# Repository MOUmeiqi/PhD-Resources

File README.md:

# PhD-Resources
Source code repository for PhD on OCDM-aEITS

*** README ***

This repository (repo) contains the source code and some experimental results acquired during research of the thesis titled "Absolute Electrical Impedance Tomography and Spectroscopy - An Orthogonal Chirp Division Multiplexed (OCDM) Approach"
This thesis was authored by: Ezra Luke America and presented to the University of Cape Town for fulfilment of a Doctorate of Philosophy in Electrical Engineering.

The repo separated into four streams:
1) Source Codes
2) Misc. Experimental Results
3) Schematics
4) Misc. Images

*** Codes ***
The source codes components of the repo holds the source files that were used for the Arduino, MATLAB, uDAQ, and FPGA.
The code for the Arduino was used to control the system wide multiplexing.
The code for MATLAB was used to control the entire system and reconstruct images.
The code for the uDAQ_test_scripts were used to control a data acquisition card when initial tests were performed.
The code for the VHDL_CODE were used to control the ADC/DAC data acquisition board and FPGA.

*** Misc. Experimental Results ***
This folder contains 8 internal folders that hold a measurement frame for eight different positions of an anomaly.
To test this data, import the data to the MATLAB image_reconstruction code in the MATLAB folder.

*** Schematics ***
The schematics folder contains some system design schematics.

*** Misc. Images ***
This folder contains some reconstructed images using higher element FEM models.

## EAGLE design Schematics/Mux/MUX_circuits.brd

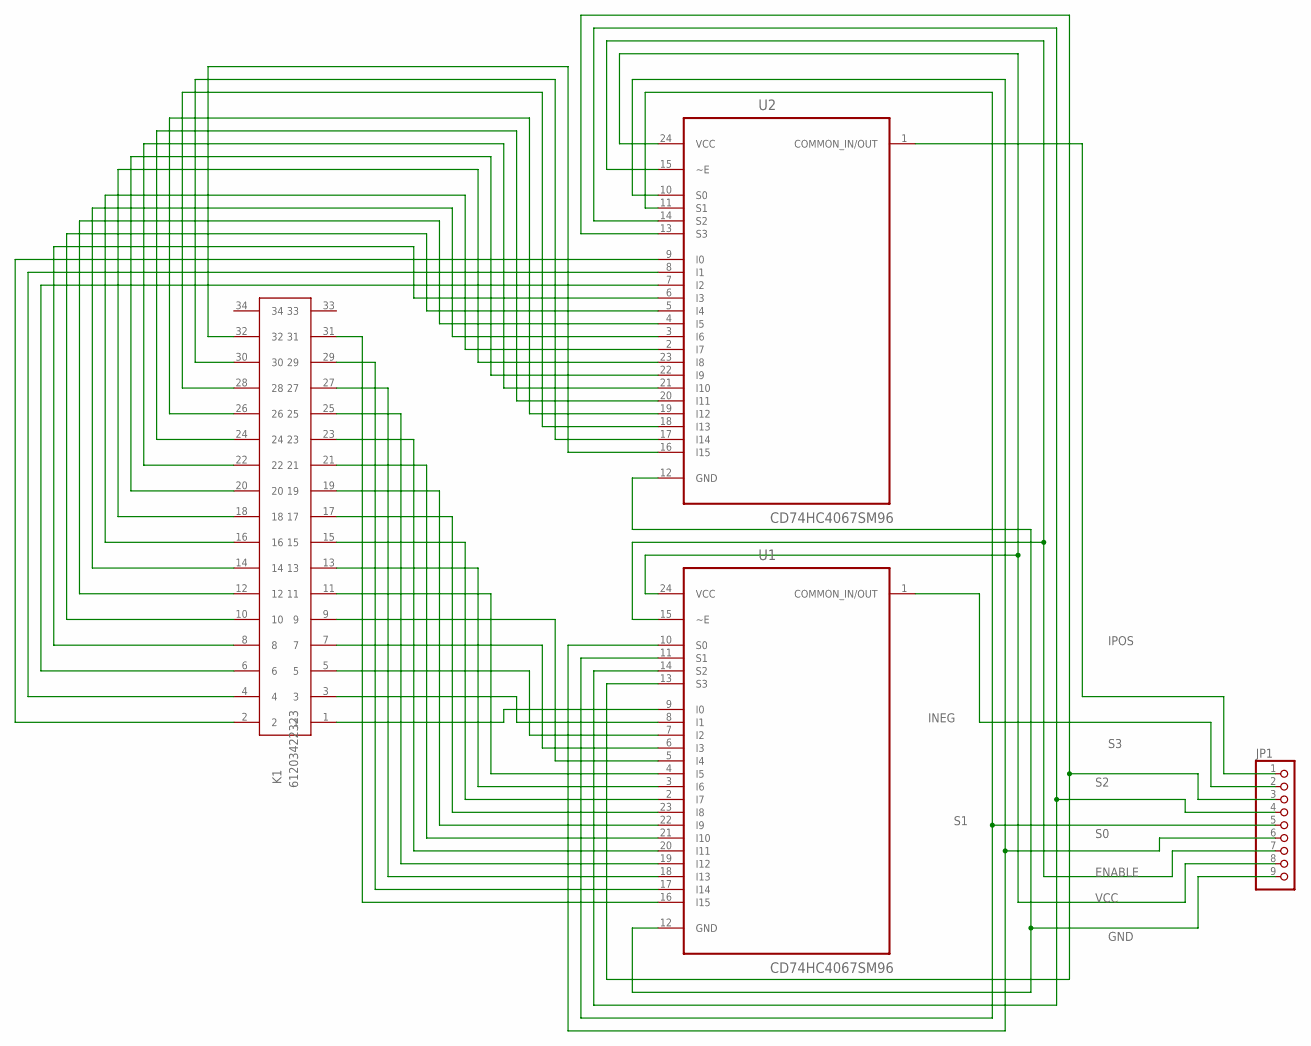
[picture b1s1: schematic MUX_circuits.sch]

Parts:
JP1: PINHD-1X9; 1X09
K1: 61203422323
U1, U2: CD74HC4067SM96; SOP65P780X200-24N

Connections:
ENABLE: JP1.7, U1.15 (~E), U2.15 (~E)
GND: JP1.9, U1.12 (GND), U2.12 (GND)
INEG: JP1.2, U1.1 (COMMON_IN/OUT)
IPOS: JP1.1, U2.1 (COMMON_IN/OUT)
unnamed: K1.1, U1.9 (I0)
unnamed: K1.2, U2.9 (I0)
unnamed: K1.3, U1.8 (I1)
unnamed: K1.5, U1.7 (I2)
unnamed: K1.7, U1.6 (I3)
unnamed: K1.9, U1.5 (I4)
unnamed: K1.11, U1.4 (I5)
unnamed: K1.13, U1.3 (I6)
unnamed: K1.15, U1.2 (I7)
unnamed: K1.17, U1.23 (I8)
unnamed: K1.19, U1.22 (I9)
unnamed: K1.21, U1.21 (I10)
unnamed: K1.23, U1.20 (I11)
unnamed: K1.25, U1.19 (I12)
unnamed: K1.27, U1.18 (I13)
unnamed: K1.29, U1.17 (I14)
unnamed: K1.31, U1.16 (I15)
unnamed: K1.4, U2.8 (I1)
unnamed: K1.6, U2.7 (I2)
unnamed: K1.8, U2.6 (I3)
unnamed: K1.10, U2.5 (I4)
unnamed: K1.12, U2.4 (I5)
unnamed: K1.14, U2.3 (I6)
unnamed: K1.16, U2.2 (I7)
unnamed: K1.18, U2.23 (I8)
unnamed: K1.20, U2.22 (I9)
unnamed: K1.22, U2.21 (I10)
unnamed: K1.24, U2.20 (I11)
unnamed: K1.26, U2.19 (I12)
unnamed: K1.28, U2.18 (I13)
unnamed: K1.30, U2.17 (I14)
unnamed: K1.32, U2.16 (I15)
S0: JP1.6, U1.10 (S0), U2.10 (S0)
S1: JP1.5, U1.11 (S1), U2.11 (S1)
S2: JP1.4, U1.14 (S2), U2.14 (S2)
S3: JP1.3, U1.13 (S3), U2.13 (S3)
VCC: JP1.8, U1.24 (VCC), U2.24 (VCC)

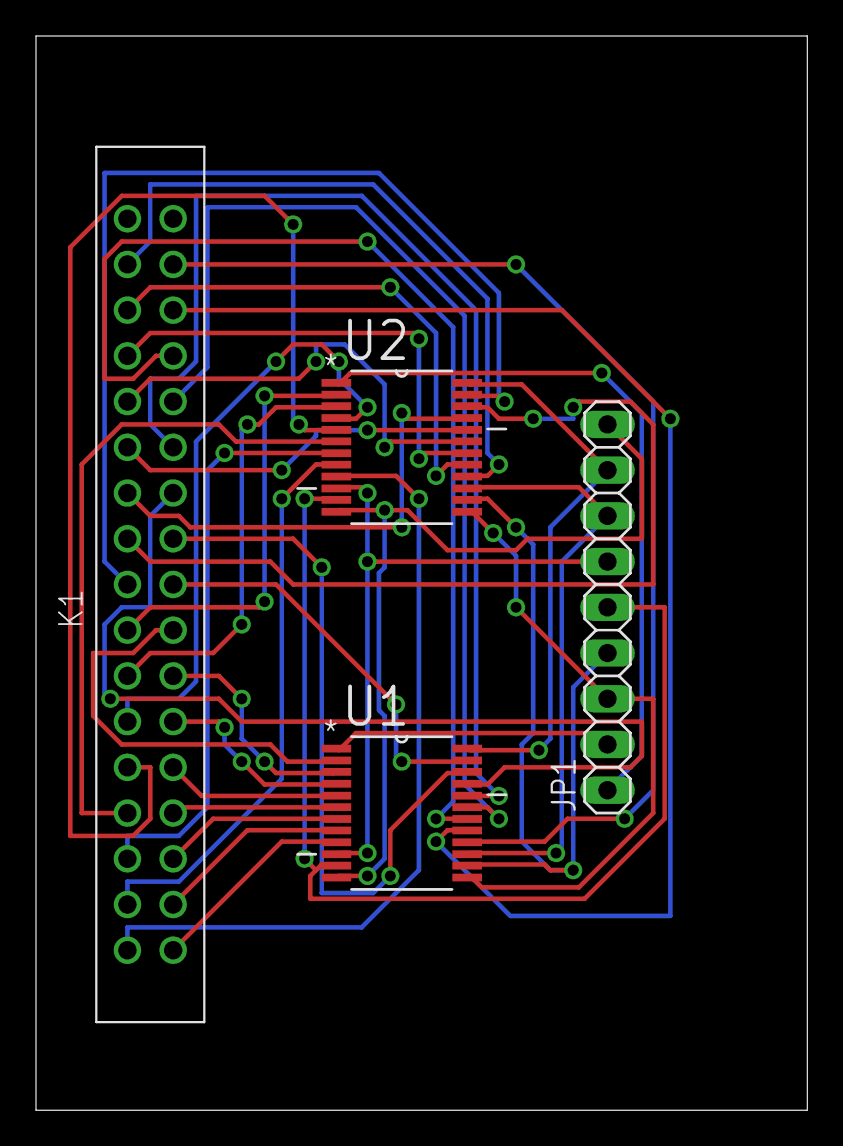
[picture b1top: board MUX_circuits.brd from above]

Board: 2 copper layers, 42.9 x 59.7 mm, 4 parts (0 on the bottom side), 41 nets.

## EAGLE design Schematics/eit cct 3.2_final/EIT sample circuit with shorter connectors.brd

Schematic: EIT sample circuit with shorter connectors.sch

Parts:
C3, C4: C-US050-030X075; C050-030X075
K1, K2, K3, K4: 61203422323
R67, R68, R69, R70, R71, R72, R73, R74, R75, R76, R77, R78, R79, R80, R81, R82, R83, R84, R85, R86, R87, R88, R89, R90, R91, R92, R93, R94, R95, R96, R97, R98: R-US_0207/10; 0207/10
R99, R100, R101, R102, R103, R104, R105, R106, R107, R108, R109, R110, R111, R112, R113, R114, R115, R116, R117, R118, R119, R120, R121, R122, R123, R124, R125, R126, R127, R128, R129, R130: R-US_0207/7; 0207/7
U1: LTC2418CGNPBF; SOP63P600X175-28N
U2, U3, U4, U5: CD74HC4067SM96; SOP65P780X200-24N
U$1, U$2, U$3, U$4, U$5, U$6, U$7, U$8, U$9, U$10, U$11, U$12, U$13, U$14, U$15, U$16: MCP601-I/SN; SOIC127P600X175-8N

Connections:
GND: C3.2, C4.2, K4.16, U1.10 (COM), U1.12 (REF-), U1.15 (GND), U2.12 (GND), U3.12 (GND), U4.12 (GND), U5.12 (GND), U$1.4 (VSS), U$2.4 (VSS), U$3.4 (VSS), U$4.4 (VSS), U$5.4 (VSS), U$6.4 (VSS), U$7.4 (VSS), U$8.4 (VSS), U$9.4 (VSS), U$10.4 (VSS), U$11.4 (VSS), U$12.4 (VSS), U$13.4 (VSS), U$14.4 (VSS), U$15.4 (VSS), U$16.4 (VSS)
unnamed: R67.2, U1.21 (CH0), U$16.6 (VOUT)
unnamed: R71.2, U1.23 (CH2), U$14.6 (VOUT)
unnamed: R73.2, U1.24 (CH3), U$12.6 (VOUT)
unnamed: R75.2, U1.25 (CH4), U$11.6 (VOUT)
unnamed: R77.2, U1.26 (CH5), U$10.6 (VOUT)
unnamed: R79.2, U1.27 (CH6), U$9.6 (VOUT)
unnamed: R81.2, U1.28 (CH7), U$8.6 (VOUT)
unnamed: R83.2, U1.1 (CH8), U$1.6 (VOUT)
unnamed: R85.2, U1.2 (CH9), U$2.6 (VOUT)
unnamed: R87.2, U1.3 (CH10), U$3.6 (VOUT)
unnamed: R89.2, U1.4 (CH11), U$4.6 (VOUT)
unnamed: R91.2, U1.5 (CH12), U$5.6 (VOUT)
unnamed: R93.2, U1.6 (CH13), U$6.6 (VOUT)
unnamed: R95.2, U1.7 (CH14), U$7.6 (VOUT)
unnamed: R97.2, U1.8 (CH15), U$13.6 (VOUT)
unnamed: K4.3, R68.1, R70.1, R72.1, R74.1, R76.1, R78.1, R80.1, R82.1, R84.1, R86.1, R88.1, R90.1, R92.1, R94.1, R96.1, R98.1
unnamed: R94.2, R103.1, U$6.3 (VIN+)
unnamed: R92.2, R105.1, U$5.3 (VIN+)
unnamed: R67.1, R130.1, U$16.2 (VIN-)
unnamed: R90.2, R107.1, U$4.3 (VIN+)
unnamed: R68.2, R129.1, U$16.3 (VIN+)
unnamed: R88.2, R109.1, U$3.3 (VIN+)
unnamed: R69.1, R128.1, U$15.2 (VIN-)
unnamed: R70.2, R127.1, U$15.3 (VIN+)
unnamed: R86.2, R111.1, U$2.3 (VIN+)
unnamed: R71.1, R126.1, U$14.2 (VIN-)
unnamed: R84.2, R113.1, U$1.3 (VIN+)
unnamed: R82.2, R115.1, U$8.3 (VIN+)
unnamed: R73.1, R124.1, U$12.2 (VIN-)
unnamed: R80.2, R117.1, U$9.3 (VIN+)
unnamed: R75.1, R122.1, U$11.2 (VIN-)
unnamed: R78.2, R119.1, U$10.3 (VIN+)
unnamed: R77.1, R120.1, U$10.2 (VIN-)
unnamed: R76.2, R121.1, U$11.3 (VIN+)
unnamed: R79.1, R118.1, U$9.2 (VIN-)
unnamed: R74.2, R123.1, U$12.3 (VIN+)
unnamed: R81.1, R116.1, U$8.2 (VIN-)
unnamed: R72.2, R125.1, U$14.3 (VIN+)
unnamed: R83.1, R114.1, U$1.2 (VIN-)
unnamed: K1.2, R129.2
unnamed: R85.1, R112.1, U$2.2 (VIN-)
unnamed: K1.1, R130.2
unnamed: R87.1, R110.1, U$3.2 (VIN-)
unnamed: K1.4, R127.2
unnamed: R89.1, R108.1, U$4.2 (VIN-)
unnamed: K1.3, R128.2
unnamed: R91.1, R106.1, U$5.2 (VIN-)
unnamed: K1.6, R125.2
unnamed: R93.1, R104.1, U$6.2 (VIN-)
unnamed: K1.5, R126.2
unnamed: R95.1, R102.1, U$7.2 (VIN-)
unnamed: K1.8, R123.2
unnamed: R97.1, R100.1, U$13.2 (VIN-)
unnamed: K1.7, R124.2
unnamed: R98.2, R99.1, U$13.3 (VIN+)
unnamed: K1.10, R121.2
unnamed: R96.2, R101.1, U$7.3 (VIN+)
unnamed: K1.9, R122.2
unnamed: K1.12, R119.2
unnamed: K1.11, R120.2
unnamed: K1.14, R117.2
unnamed: K1.19, R112.2
unnamed: K1.16, R115.2
unnamed: K1.15, R116.2
unnamed: K1.18, R113.2
unnamed: K1.17, R114.2
unnamed: K1.20, R111.2
unnamed: K4.1, U1.19 (F0)
unnamed: K1.22, R109.2
unnamed: K1.21, R110.2
unnamed: K1.24, R107.2
unnamed: K1.26, R105.2
unnamed: K1.25, R106.2
unnamed: K1.23, R108.2
unnamed: K1.28, R103.2
unnamed: K1.27, R104.2
unnamed: K1.30, R101.2
unnamed: K1.29, R102.2
unnamed: K1.32, R99.2
unnamed: K1.31, R100.2
unnamed: K2.1, U2.9 (I0)
unnamed: K2.2, U3.9 (I0)
unnamed: K2.3, U2.8 (I1)
unnamed: K2.4, U3.8 (I1)
unnamed: K2.5, U2.7 (I2)
unnamed: K2.6, U3.7 (I2)
unnamed: K2.7, U2.6 (I3)
unnamed: K2.8, U3.6 (I3)
unnamed: K2.9, U2.5 (I4)
unnamed: K2.10, U3.5 (I4)
unnamed: K2.12, U3.4 (I5)
unnamed: K2.14, U3.3 (I6)
unnamed: K2.16, U3.2 (I7)
unnamed: K2.18, U3.23 (I8)
unnamed: K2.20, U3.22 (I9)
unnamed: K2.22, U3.21 (I10)
unnamed: K2.24, U3.20 (I11)
unnamed: K2.26, U3.19 (I12)
unnamed: K2.28, U3.18 (I13)
unnamed: K2.30, U3.17 (I14)
unnamed: K2.32, U3.16 (I15)
unnamed: K2.11, U2.4 (I5)
unnamed: K2.13, U2.3 (I6)
unnamed: K2.15, U2.2 (I7)
unnamed: K2.17, U2.23 (I8)
unnamed: K2.19, U2.22 (I9)
unnamed: K2.21, U2.21 (I10)
unnamed: K2.23, U2.20 (I11)
unnamed: K2.25, U2.19 (I12)
unnamed: K2.27, U2.18 (I13)
unnamed: K2.29, U2.17 (I14)
unnamed: K2.31, U2.16 (I15)
unnamed: K3.1, U4.9 (I0)
unnamed: K3.3, U4.8 (I1)
unnamed: K3.5, U4.7 (I2)
unnamed: K3.7, U4.6 (I3)
unnamed: K3.9, U4.5 (I4)
unnamed: K3.11, U4.4 (I5)
unnamed: K3.13, U4.3 (I6)
unnamed: K3.15, U4.2 (I7)
unnamed: K3.17, U4.23 (I8)
unnamed: K3.19, U4.22 (I9)
unnamed: K3.21, U4.21 (I10)
unnamed: K3.23, U4.20 (I11)
unnamed: K3.25, U4.19 (I12)
unnamed: K3.27, U4.18 (I13)
unnamed: K3.29, U4.17 (I14)
unnamed: K3.31, U4.16 (I15)
unnamed: K3.2, U5.9 (I0)
unnamed: K3.4, U5.8 (I1)
unnamed: K3.6, U5.7 (I2)
unnamed: K3.8, U5.6 (I3)
unnamed: K3.10, U5.5 (I4)
unnamed: K3.12, U5.4 (I5)
unnamed: K3.14, U5.3 (I6)
unnamed: K3.16, U5.2 (I7)
unnamed: K3.18, U5.23 (I8)
unnamed: K3.20, U5.22 (I9)
unnamed: K3.22, U5.21 (I10)
unnamed: K3.24, U5.20 (I11)
unnamed: K3.26, U5.19 (I12)
unnamed: K3.28, U5.18 (I13)
unnamed: K3.30, U5.17 (I14)
unnamed: K3.32, U5.16 (I15)
unnamed: K4.5, U1.16 (~CS)
unnamed: K4.4, U1.18 (SCK)
unnamed: K4.8, U1.20 (SDI)
unnamed: K4.12, U1.17 (SDO)
unnamed: K4.28, U2.14 (S2), U3.14 (S2), U4.14 (S2), U5.14 (S2)
unnamed: K4.2, U2.15 (~E), U3.15 (~E)
unnamed: K1.13, R118.2
unnamed: K4.22, U4.15 (~E), U5.15 (~E)
unnamed: K4.26, U2.11 (S1), U3.11 (S1), U4.11 (S1), U5.11 (S1)
unnamed: K4.30, U2.13 (S3), U3.13 (S3), U4.13 (S3), U5.13 (S3)
unnamed: R69.2, U1.22 (CH1), U$15.6 (VOUT)
unnamed: K4.34, U2.1 (COMMON_IN/OUT), U4.1 (COMMON_IN/OUT)
unnamed: K4.33, U3.1 (COMMON_IN/OUT), U5.1 (COMMON_IN/OUT)
unnamed: K4.24, U2.10 (S0), U3.10 (S0), U4.10 (S0), U5.10 (S0)
VCC: C3.1, C4.1, K4.14, U1.9 (VCC), U1.11 (REF+), U2.24 (VCC), U3.24 (VCC), U4.24 (VCC), U5.24 (VCC), U$1.7 (VDD), U$2.7 (VDD), U$3.7 (VDD), U$4.7 (VDD), U$5.7 (VDD), U$6.7 (VDD), U$7.7 (VDD), U$8.7 (VDD), U$9.7 (VDD), U$10.7 (VDD), U$11.7 (VDD), U$12.7 (VDD), U$13.7 (VDD), U$14.7 (VDD), U$15.7 (VDD), U$16.7 (VDD)

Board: 2 copper layers, 91 parts (0 on the bottom side), 160 nets, no tracks yet.

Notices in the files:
parts and their libraries:
Wire_to_Board_Connectors_rev15d: Copyright: Würth Elektronik
